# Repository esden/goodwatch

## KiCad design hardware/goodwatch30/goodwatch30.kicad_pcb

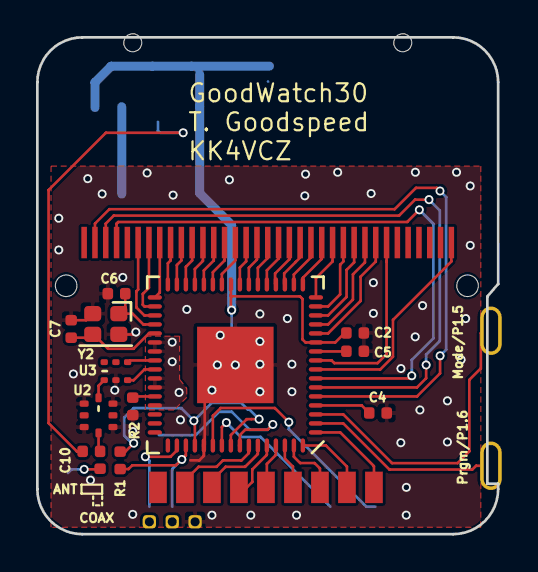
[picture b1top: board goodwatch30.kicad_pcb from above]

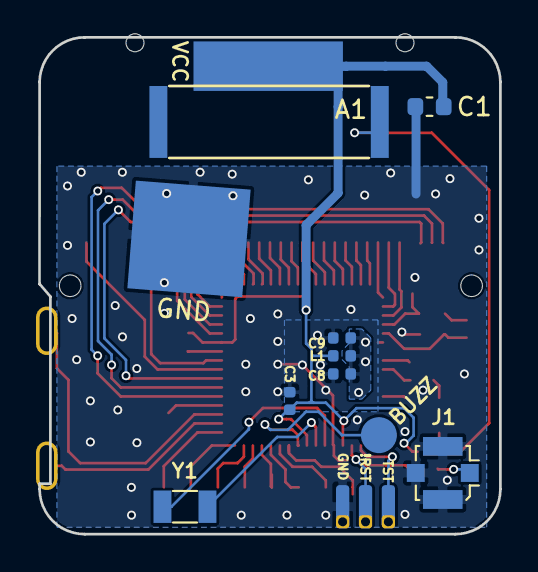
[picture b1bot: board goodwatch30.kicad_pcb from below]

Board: 2 copper layers, 25.6 x 27.6 mm, 23 parts (8 on the bottom side), 57 nets.

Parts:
A1: YageoS432
BRD1: CA53BOARD; ca53board
C1: 47uF; C_0603_1608Metric
C2, C3, C8, C9: 0.1uF; C_0402_1005Metric
C4: 10uF; C_0402_1005Metric
C5: 0.47uF; C_0402_1005Metric
C6, C7: 19pF; C_0402_1005Metric
C10: 220pF; C_Jumper_0402_1005Metric
J1: ANT_U.FL; U.FL_Molex_MCRF_73412-0110_Vertical
KPD1: CA53KEYPAD; ca53keypad
L1: L_Small; L_0402_1005Metric
LCD1: CA53LCD; ca53lcd
R1: 75k; R_0402_1005Metric
R2: 56k; R_0402_1005Metric
U1: CC430F613x
U2: 0915LP15B02; LP15
U3: B0310J50100AHF
Y1: 32.768kHz; Crystal_SMD_3215-2Pin_3.2x1.5mm
Y2: FA128 26MHz; FA128

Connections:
/!RST: BRD1.6, R1.2, U1.51
/BUZZ: BRD1.8, U1.57
/COM0: LCD1.2, U1.5
/COM1: LCD1.3, U1.6
/COM2: LCD1.4, U1.7
/LCDCAP: C4.1, U1.4
/RFVCC: C8.1, C9.1, L1.1, U1.38, U1.39, U1.42, U1.43, U1.45
/RF_N: U1.41, U3.3
/RF_P: U1.40, U3.4
/RF_XIN: C6.1, U1.36, Y2.1
/RF_XOUT: C7.1, U1.37, Y2.3
/TST: BRD1.5, U1.50
/VCORE: C5.1, U1.10
GND: BRD1.2, BRD1.7, C1.2, C2.2, C3.2, C4.2, C5.2, C6.2, C7.2, C8.2, C9.2, J1.2, R2.2, U1.53, U1.65, U2.1, U2.3, U2.5, U2.7, U3.2, Y2.2, Y2.4
unnamed: A1.1, C10.2
unnamed: BRD1.3, U1.3
unnamed: BRD1.4, U1.2
unnamed: C10.1, U2.4
unnamed: C10.3, J1.1
unnamed: KPD1.2, U1.58
unnamed: KPD1.3, U1.59
unnamed: KPD1.4, U1.60
unnamed: KPD1.5, U1.61
unnamed: KPD1.6, U1.62
unnamed: KPD1.7, U1.63
unnamed: KPD1.8, U1.64
unnamed: KPD1.9, U1.1
unnamed: LCD1.6, U1.35
unnamed: LCD1.7, U1.34
unnamed: LCD1.8, U1.33
unnamed: LCD1.9, U1.32
unnamed: LCD1.10, U1.31
unnamed: LCD1.11, U1.30
unnamed: LCD1.12, U1.29
unnamed: LCD1.13, U1.28
unnamed: LCD1.14, U1.27
unnamed: LCD1.15, U1.26
unnamed: LCD1.16, U1.24
unnamed: LCD1.17, U1.23
unnamed: LCD1.18, U1.22
unnamed: LCD1.19, U1.21
unnamed: LCD1.20, U1.20
unnamed: LCD1.21, U1.19
unnamed: LCD1.22, U1.18
unnamed: LCD1.23, U1.17
unnamed: LCD1.24, U1.16
unnamed: LCD1.25, U1.15
unnamed: LCD1.26, U1.14
unnamed: LCD1.27, U1.13
unnamed: LCD1.28, U1.12
unnamed: LCD1.29, U1.9
unnamed: LCD1.35, U1.8
unnamed: R2.1, U1.44
unnamed: U1.54, Y1.2
unnamed: U1.55, Y1.1
unnamed: U2.8, U3.1
VCC: BRD1.1, C1.1, C2.1, C3.1, L1.2, R1.1, U1.11, U1.25, U1.52, U1.56

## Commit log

2018-09-03 Minor routing cleanup on pin 35
2018-09-05 Added a symbol for a capacitor based jumper
2018-09-05 Added C_Jumper to switch between the antenna and coax
2018-09-05 Reshaped and replaced spy-bi-wire testpoints
2018-09-05 Added footprint for a 0402 capacitor jumper
2018-09-05 Placed u.fl coax connector insight a hole of the battery pastic frame.
    I replaced the 220pF block cap in front of the antenna with a cap jumper to switch between the antenna and the u.fl coax connector.
    To create some space for the coax connector I modified the casio board footprint. At the footprint I moved and reshaped the spy-bi-wire pads.
    Travis used clip connectors on one of the photos so I added some holes to to pads. If it is not possible to use clip connectors we could solder a 50 mil header or cable on to these pads (maybe even u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
    The u.fl connector is placed at the approximate position of the hole in the pastic frame (this might not fit since I am still mis
